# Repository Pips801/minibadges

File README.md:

# SAINTCON Minibadges
All of my Minibadges, including costs, files, and vendors.

# 2026

## IPEX to SMA adapter Minibadge
### Images

### Description
A minibadge (meant for use with my Meshtastic Minibadge) that converts I-PEX to SMA, so you can have a vertical SMA antenna.

## Phone charger Minibadge
### Images

### Description
Have you ever needed to charge your phone (or other stuff), but all you have lying around is a SAINTCON badge? You’re in luck! This minibadge will charge (up to 500mA) anything USB-C that you plug into it! Charge your phone! Charge your headphones! Charge a laptop! (not really) Charge another badge! The world is your ~oyster~ charger!

## BOM (post-tariffs)
| Vendor          | Item                   | Item total | Item quantity | Per item cost | Per unit cost | Per unit required |
| --------------- | ---------------------- | ---------- | ------------- | ------------- | ------------- | ----------------- |
| JLC PCB         | Board                  | $5.00      | 30            | $0.17         | $0.17         | 1                 |
| JLC Assembly    | Setup fee              | $8.00      | 30            | $0.27         | $0.27         | 1                 |
| JLC Assembly    | Stencil                | $1.50      | 30            | $0.05         | $0.05         | 1                 |
| JLC Assembly    | Components             | $17.11     | 30            | $0.57         | $0.57         | 1                 |
| JLC Assembly    | Extended component fee | $12.00     | 30            | $0.40         | $0.40         | 1                 |
| JLC Assembly    | Assembly fee           | $2.29      | 30            | $0.08         | $0.08         | 1                 |
| Shipping        | Shipping               | $13.35     | 30            | $0.45         | $0.45         | 1                 |
| Tariffs & taxes | Sales Tax              | $4.08      | 30            | $0.14         | $0.14         | 1                 |

| Project total cost | Per unit total cost | Quantity | Adjusted total | Adjusted per unit cost |
| ------------------ | ------------------- | -------- | -------------- | ---------------------- |
| $63.33             | $2.11               | 30       | $63.33         | $2.11                  |

## Seeed XIAO ESP32 Minibadge
### Images

## Description
A Minibadge that can hold and power the Seeed XIAO ESP32 modules. It features 1206 diodes to prevent the XIAO from backfeeding power to the main badge, should you plug USB in at the same time. The Minibadge has solderable jumper pads to connect 3.3v, 5v, SDA, and SCL to your ESP. This is untested, and will be updated, but I recommend just soldering the 3.3V pad. I would like to see if it's at all possible for the badge next year to work with this badge over I2C.

Supports:
* [XIAO ESP32-S3 + Wio-SX1262 (Meshtastic)](https://www.seeedstudio.com/Wio-SX1262-with-XIAO-ESP32S3-p-5982.html)
* [XIAO ESP32-C6 (Thread/Zigbee)](https://www.seeedstudio.com/Seeed-Studio-XIAO-ESP32C6-p-5884.html)
* [XIAO ESP32-S3 Sense (Camera/SD card)](https://www.seeedstudio.com/XIAO-ESP32S3-Sense-p-5639.html)
* Other XIAO ESPs are untested, but if the pinout is the same, it will work.

Possible projects:
* [Meshtastic node minibadge](https://www.seeedstudio.com/Wio-SX1262-with-XIAO-ESP32S3-p-5982.html)
* [Zigbee node minibadge](https://www.seeedstudio.com/Seeed-Studio-XIAO-ESP32C6-p-5884.html)
* [Picture/video recorder minibadge](https://www.seeedstudio.com/XIAO-ESP32S3-Sense-p-5639.html)
* [LED matrix minibadge](https://www.seeedstudio.com/6x10-RGB-MATRIX-for-XIAO-p-5771.html)
* [GNSS minibadge](https://www.seeedstudio.com/L76K-GNSS-Module-for-Seeed-Studio-XIAO-p-5864.html)
* [Temp/humidity/light sensor minibadge](https://www.seeedstudio.com/XIAO-LOG-p-6341.html)
* [mmWave sensor minibadge](https://www.seeedstudio.com/Seeed-Studio-XIAO-24Ghz-mmwave-Human-Static-Presence-Module-p-6266.html)

# 2025

## Glitch Gallery
### Images

### Description
A secret Minibadge for a secret event. 

### BOM (post-tariffs)
| Vendor       | Item            | Item total | Item quantity | Per item cost | Per unit cost | Per unit required |
| ------------ | --------------- | ---------- | ------------- | ------------- | ------------- | ----------------- |
| JLC PCB      | Board           | $4.40      | 200           | $0.02         | $0.02         | 1                 |
| JLC PCB      | Engineering fee | $8.00      | 200           | $0.04         | $0.04         | 1                 |
| JLC PCB      | Deburring       | $4.30      | 200           | $0.02         | $0.02         | 1                 |
| JLC PCB      | Confirmation    | $1.00      | 200           | $0.01         | $0.01         | 1                 |
| JLC PCB      | Packaging       | $0.71      | 200           | $0.00         | $0.00         | 1                 |
| JLC PCB      | Film            | $0.20      | 200           | $0.00         | $0.00         | 1                 |
| JLC Tariffs  | Tariffs         | $10.23     | 200           | $0.05         | $0.05         | 1                 |
| JLC Shipping | Shipping        | $22.95     | 200           | $0.11         | $0.11         | 1                 |
| Amazon       | Bags            | $20.00     | 2000          | $0.01         | $0.01         | 1                 |
| Amazon       | Pins            | $39.00     | 16000         | $0.00         | $0.01         | 4                 |

| Quantity | Project total cost | Per unit total cost | Actual total | Actual per unit cost |
| -------- | ------------------ | ------------------- | ------------ | -------------------- |
| 200      | $110.79            | $0.55               | $55.74       | $0.28                |

## Microbadge Minibadge
### Images

### Description
A Minibadge that can hold 6 Microbadges! Supports the [Microbadge V2](https://github.com/Pips801/microbadge/) standard. This is my first 4 layer board!

### BOM (post-tariffs)
| Vendor       | Item            | Item total | Item quantity | Per item cost | Per unit cost | Per unit required |
| ------------ | --------------- | ---------- | ------------- | ------------- | ------------- | ----------------- |
| JLC PCB      | Board           | $6.90      | 250           | $0.03         | $0.03         | 1                 |
| JLC PCB      | Engineering fee | $24.00     | 250           | $0.10         | $0.10         | 1                 |
| JLC PCB      | Film            | $0.20      | 250           | $0.00         | $0.00         | 1                 |
| JLC PCB      | Testing         | $0.80      | 250           | $0.00         | $0.00         | 1                 |
| JLC PCB      | Deburring       | $5.40      | 250           | $0.02         | $0.02         | 1                 |
| JLC PCB      | Silkscreen tech | $16.20     | 250           | $0.06         | $0.06         | 1                 |
| JLC PCB      | Color           | $4.80      | 250           | $0.02         | $0.02         | 1                 |
| JLC Shipping | Shipping (UPS)  | $10.20     | 250           | $0.04         | $0.04         | 1                 |
| Amazon       | Bags            | $20.00     | 2000          | $0.01         | $0.01         | 1                 |
| Amazon       | Pins            | $39.00     | 16000         | $0.00         | $0.04         | 16                |

| Project total cost | Per unit total cost | Quantity | Adjusted total | Adjusted per unit cost |
| ------------------ | ------------------- | -------- | -------------- | ---------------------- |
| $127.50            | $0.28               | 450      | $145.35        | $0.32                  |

## Julia Reagan
### Images

### Description
Wife, Mother, and Grandmother. We will miss her!

### BOM (post-tariffs)
| Vendor       | Item                    | Item total | Item quantity | Per item cost | Per unit cost | Per unit required |
| ------------ | ----------------------- | ---------- | ------------- | ------------- | ------------- | ----------------- |
| JLC PCB      | Board                   | $25.50     | 450           | $0.06         | $0.06         | 1                 |
| JLC PCB      | Engineering fee         | $8.00      | 450           | $0.02         | $0.02         | 1                 |
| JLC PCB      | Film                    | $3.00      | 450           | $0.01         | $0.01         | 1                 |
| JLC PCB      | Confirm production file | $1.00      | 450           | $0.00         | $0.00         | 1                 |
| JLC PCB      | Silkscreen tech         | $4.72      | 450           | $0.01         | $0.01         | 1                 |
| JLC Assembly | Components              | $12.21     | 450           | $0.03         | $0.03         | 1                 |
| JLC Assembly | SMT assembly            | $5.70      | 450           | $0.01         | $0.01         | 1                 |
| JLC Assembly | Setup fee               | $25.00     | 450           | $0.06         | $0.06         | 1                 |
| JLC Assembly | Packaging fee           | $0.47      | 450           | $0.00         | $0.00         | 1                 |
| JLC Assembly | De-panel boards         | $17.29     | 450           | $0.04         | $0.04         | 1                 |
| JLC Assembly | Stencil                 | $7.89      | 450           | $0.02         | $0.02         | 1                 |
| JLC Assembly | Component fee           | $3.00      | 450           | $0.01         | $0.01         | 1                 |
| JLC Assembly | Confirm parts           | $0.43      | 450           | $0.00         | $0.00         | 1                 |
| JLC          | Shipping (UPS)          | $56.40     | 450           | $0.13         | $0.13         | 1                 |
| JLC          | Tariffs                 | $60.73     | 450           | $0.13         | $0.13         | 1                 |
| Amazon       | Bags                    | $19.99     | 2000          | $0.01         | $0.01         | 1                 |
| Amazon       | Pins                    | $39.00     | 16000         | $0.00         | $0.02         | 8                 |

| Project total cost | Per unit total cost | Quantity | Adjusted total | Adjusted per unit cost |
| ------------------ | ------------------- | -------- | -------------- | ---------------------- |
| $290.33            | $0.65               | 450      | $244.61        | $0.54                  |

## Crown Burger Minibadge
### Images
    
### Description
Do you love Fry sauce? because we sure do. We also love Crown Burger, whom we are beholdent to.

### BOM (post-tarrifs)
| Vendor | Item     | Item total | Item quantity | Per item cost | Per unit cost | Per unit required |
| ------ | -------- | ---------- | ------------- | ------------- | ------------- | ----------------- |
| JLCPCB | PCB      | $17.30     | 120           | $0.14         | $0.14         | 1                 |
| JLCPCB | Assembly | $32.96     | 120           | $0.27         | $0.27         | 1                 |
| JLCPCB | Shipping | $37.80     | 120           | $0.32         | $0.32         | 1                 |
| Amazon | Bags     | $19.99     | 2000          | $0.01         | $0.01         | 1                 |
| Amazon | Pins     | $39.00     | 16000         | $0.00         | $0.02         | 8                 |

| Project total cost | Per unit total cost | Quantity | Adjusted total | Adjusted per unit cost |
| ------------------ | ------------------- | -------- | -------------- | ---------------------- |
| $147.05            | $1.23               | 120      | $91.60         | $0.76                  |

## ATtiny DEVBOARD
### Images
     
### Description
ATTiny-816/1616 Minibadge Devboard with breakouts for USART, I2C, DAC, and SPI, as well as two LEDs. There is also support for two ADC (analog to digital conversion) inputs and two PTC (touch sense) pins. It is programmed using UPDI via pin 6 (PROG4). either has 8KB or 16KB of flash
### Assembly
Solder pin headers. DO NOT PLUG BOARD IN UPSIDE-DOWN!!!!
### BOM
| Description/Link 	| Item      	| Item total 	| Item quantity 	| Per item cost 	| Per unit cost 	|  Per unit required 	|
|------------------	|-----------	|------------	|---------------	|---------------	|---------------	|--------------------	|
| JLCPCB assembly  	| Minibadge 	|     $68.02 	|            50 	|         $1.36 	|         $1.36 	|                  1 	|
| Amazon           	| Pins      	|      $5.49 	|           800 	|         $0.01 	|         $0.11 	|                 16 	|

| Project total cost 	| Per unit total cost 	| Adjusted quantity 	| Adjusted total 	|
|--------------------	|---------------------	|-------------------	|----------------	|
|             $73.51 	|               $1.47 	|                50 	|         $73.51 	|

## BEEP BEEP Minibadge
### Images

### Descrption
An obnoxiously-loud buzzer with an obnoxiously bright and large button. How tempting! Who wouldn't want to press that? Due to the length of the buzzer, the minibadge needs extra-long pin headers to connect snug with the socket.
### Assembly Instructions
First, solder all of the LEDs and resistors. if you are missing R1 (a potentiometer), the simply bridge the pad that says "NO R1" with solder. The potentiometer is meant for volume control. Next, solder the buzzer on the back of the badge, then with some good cutters, snip the leads of the speaker as flush as you can get them. After that, solder the comically large button on the front.

## Problem Jeep
### Images
### Description
A reversable minibadge, first of its kind! It can be used both directions, and features LEDs and resistors especially for each orientation.

## 3x3 Minibadge Display
### Images

### Description
A 3x3 Minibadge display with the same clock module as the 10x10 minibadge grid.. The USB-C port is Charge only and is configured with a 5.1k pulldown resistor to request 5V, however you are limited to approx 500mA@3.3v from the DC-DC converter. 
### Assembly Instructions
Using a pre-soldered minibadge as a guide/holder, solder all pin sockets. Screw Acrylic plate on. Stick feet pads on bottom.

## 2x2 Minibadge Display
### Images

### Description
A compact 2x2 Minibadge display with the same clock module as the 10x10 minibadge grid. If this device works well, it can be scaled up to 10 minibadges (probaby 9, 3x3 grid) without changing out any components or altering the diagram. The USB-C port is Charge only and is configured with a 5.1k pulldown resistor to request 5V, however you are limited to approx 500mA from the DC-DC converter. 
### Assembly Instructions
Using a pre-soldered minibadge as a guide/holder, solder all pin sockets.

## Doug Dimmadome's Dimma-Minibadge
### Images

## Framework Laptop Expansion slot to Minibadge
### Images

### [Instructions](https://github.com/Pips801/minibadges/blob/main/Framework%20Expansion%20Card%20Minibadge/README.md)

## Flipper Zero to Minibadge add-on
### Images

### Instructions
Solder the 1x10 pin header row downwards. Solder the 2x 1x8 pin sockets facing upwards. Optionally, bridge the SDA and SCL pads and use a Flipper Zero app that can read I2C communications. Do not bridge the CLK pad - it does not work correctly for badges that use CLK for alternating light patters.

## I almost DIED at the CheckPoint party
### Images

### Description
Some poor soul partied so hard at the 2024 checkpoint party that they died. poor guy. This minibadge is in his honor. RIP.

## The Internet
### Images

### Description
This, Jen, is the Internet. 
### Assembly
First, solder the through-hole resistor on the back side of the minibadge, and then snip the legs around the front. Next, take the black box, and insert the LED into the hole in the box. Ensure that the LED is pushed down as far as it can be and is snug. Next, put the LED legs through the correct holes (long +, short -) and line up the LED and box on the board. Hot-glue/super-glue the box onto the board, and then solder the legs of the LED. Last, solder the Minibadge's pin legs. If assembled correctly, it should blink red on and off (the LED has an IC that makes it blink)
### BOM
| Description/Link 	| Item 	| Item total 	| Item quantity 	| Per item cost 	| Per unit cost 	|  Per unit required 	|
|------------------	|------	|------------	|---------------	|---------------	|---------------	|--------------------	|
| JLCPCB           	| PCBs 	|      $9.93 	|           100 	|         $0.10 	|         $0.10 	|                  1 	|
| Amazon           	| LEDs 	|      $5.99 	|           100 	|         $0.06 	|         $0.06 	|                  1 	|

## Hang in there!
### Images

### Description
Hang in there! You've got this!
### BOM
| Description/Link  	| Item 	| Item total 	| Item quantity 	| Per item cost 	| Per unit cost 	|  Per unit required 	|
|-------------------	|------	|------------	|---------------	|---------------	|---------------	|--------------------	|
| JLCPCB + Assembly 	| PCBs 	|    $130.80 	|           400 	|         $0.33 	|         $0.33 	|                  1 	|

## Bible Study at ABGs
### Images

### Description
Sacrilegious Minibadge. You can only get this minibadge if you go to the one bar in provo during SAINTCON. If I see you're from the con, I'll give you one.
### BOM
| Description/Link  	| Item 	| Item total 	| Item quantity 	| Per item cost 	| Per unit cost 	|  Per unit required 	|
|-------------------	|------	|------------	|---------------	|---------------	|---------------	|--------------------	|
| JLCPCB + Assembly 	| PCBs 	|     $33.79 	|            50 	|         $0.68 	|         $0.68 	|                  1 	|
| Amazon            	| Bags 	|      $5.05 	|           100 	|         $0.05 	|         $0.05 	|                  1 	|
| Amazon            	| Pins 	|      $5.49 	|           800 	|         $0.01 	|         $0.05 	|                  8 	|

| Project total cost 	| Per unit total cost 	| Adjusted quantity 	| Adjusted total 	|
|--------------------	|---------------------	|-------------------	|----------------	|
|             $44.33 	|               $0.78 	|                50 	|         $39.06 	|

## Full Color Pipscat
### Images

### Description
Full color silkscreening process. The process sucked, and I was forced to learn EasyEDA in order to generate the files that JLCPCB will accept (surprise, it's super annoying and even if you do it right, it goes wrong.) 
The whole process sucked, and while I'm excited to have these badges, I am gonna make hamster handle the BS  of color silkscreening. Maybe I can have boards assembled for cheap and then just ship them over to him.
### BOM
| Description/Link | Item | Item total | Item quantity | Per item cost | Per unit cost |  Per unit required |
|------------------|------|------------|---------------|---------------|---------------|--------------------|
| JLCPCB           | PCBs |     $35.02 |           300 |         $0.12 |         $0.12 |                  1 |

## Scratch and Sniff
### Images

### Description
A scratch and sniff minibadgebadge. Stupid idea that came about from 801 Labs. The badge has a very small scratch and sniff sticker overlayed on the front. The sticker will be one of the 5 scents I used for this project, as follows

- DNS (Wet Dirt)
- TOR (Onion)
- Zodiak's Sandals (Cheese)
- Magic Smoke (Burnt Rubber)
- Vendor Call (Manure)
  
Honestly, they all smell bad. (which was the point) I may make a second round that smells nice, that would be easier to work with.
### BOM
| Description/Link  | Item                     | Item total | Item quantity | Per item cost | Per unit cost |  Per unit required |
|-------------------|--------------------------|------------|---------------|---------------|---------------|--------------------|
| JLCPCB + Assembly | PCBs                     |    $148.34 |           400 |         $0.37 |         $0.37 |                  1 |
| Amazon            | Bags                     |     $20.00 |           400 |         $0.05 |         $0.05 |                  1 |
| Amazon            | Pins                     |     $21.96 |          3200 |         $0.01 |         $0.05 |                  8 |
| Print-a-Scent     | Scratch-n-Sniff Stickers |        $74 |           750 |         $0.10 |         $0.10 |                  1 |

| Project total cost | Per unit total cost | Adjusted quantity | Adjusted total |
|--------------------|---------------------|-------------------|----------------|
|            $264.30 |               $0.57 |               400 |        $229.77 |

# 2024

## BLANK_BADGE V3 (White and Black)
### Images

### Description
Revamped BLANK_BADGE, this time with two different colors. I messed up my board shop settings on this one, and they helpfully made them sinly pannels. I tried to get them to do it again but they have minimum sizes and I was unable to intentionally do this again.
### BOM
| Description/Link | Item | Item total | Item quantity | Per item cost | Per unit cost |  Per unit required |
|------------------|------|------------|---------------|---------------|---------------|--------------------|
| JLCPCB + Assembly | PCBs |     $61.26 |            60 |         $1.02 |         $1.02 |                  1 |
| Amazon           | Bags |      $5.05 |           100 |         $0.05 |         $0.05 |                  1 |
| Amazon           | Pins |      $5.49 |           800 |         $0.01 |         $0.05 |                  8 |

| Project total cost | Per unit total cost | Adjusted quantity | Adjusted total |
|--------------------|---------------------|-------------------|----------------|
|             $71.80 |               $1.13 |                60 |         $67.58 |

## Blank Badge V1 30ct (My first badge!)
### Images

### Description
My first ever circuit board! I made this in under 24 hours, starting at nothing.
### BOM
| Description/Link | Item     | Item total | Item quantity | Per item cost | Per unit cost |  Per unit required |
|------------------|----------|------------|---------------|---------------|---------------|--------------------|
| JLCPCB           | PCBs     |     $22.48 |            30 |         $0.75 |         $0.75 |                  1 |
| Amazon           | Bags     |      $5.05 |           100 |         $0.05 |         $0.05 |                  1 |
| Amazon           | LED      |      $9.99 |           100 |         $0.10 |         $0.10 |                  1 |
| Amazon           | Resistor |      $7.09 |           100 |         $0.07 |         $0.07 |                  1 |
| Amazon           | Pins     |      $5.49 |           800 |         $0.01 |         $0.05 |                  8 |

| Project total cost | Per unit total cost | Adjusted quantity | Adjusted total |
|--------------------|---------------------|-------------------|----------------|
|             $50.10 |               $1.03 |                30 |         $30.77 |

### Other Details

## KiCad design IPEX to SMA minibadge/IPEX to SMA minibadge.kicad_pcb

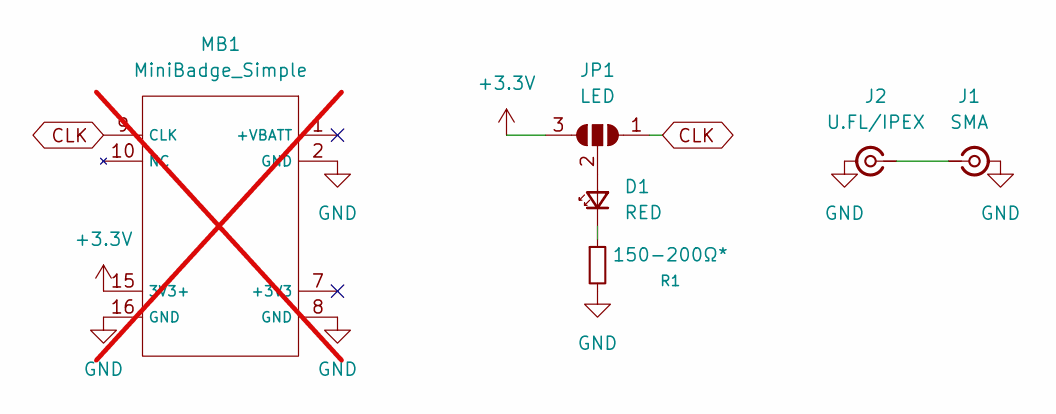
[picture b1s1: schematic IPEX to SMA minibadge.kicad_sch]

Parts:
D1: RED; LED_0805_2012Metric; LCSC Part # C84256
J1: SMA; SMA_Amphenol_132289_EdgeMount; LCSC Part # C5301850
J2: U.FL/IPEX; U.FL_Hirose_U.FL-R-SMT-1_Vertical; LCSC Part # C19078354
JP1: LED; SolderJumper-3_P1.3mm_Open_RoundedPad1.0x1.5mm_NumberLabels
MB1: MiniBadge_Simple; MiniBadge_Simple_NoEdges; not fitted
R1: 150-200Ω*; R_0603_1608Metric; LCSC Part # C22808

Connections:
+3.3V: JP1.3 (B), MB1.15 (3V3+)
CLK: JP1.1 (A), MB1.9 (CLK)
GND: J1.2 (Ext), J2.2 (Ext), MB1.2 (GND), MB1.8 (GND), MB1.16 (GND), R1.2
unnamed: D1.2 (A), JP1.2 (C)
unnamed: D1.1 (K), R1.1
unnamed: J1.1 (In), J2.1 (In)

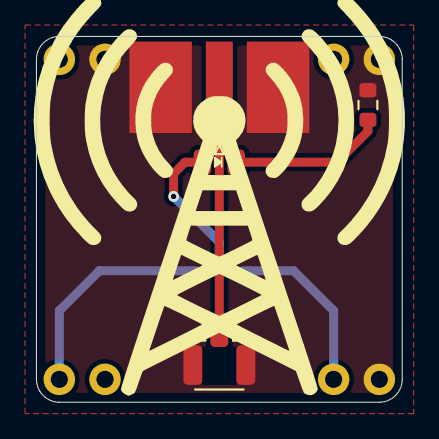
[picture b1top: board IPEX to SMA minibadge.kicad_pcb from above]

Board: 2 copper layers, 20.3 x 20.3 mm, 6 parts (1 on the bottom side), 6 nets.

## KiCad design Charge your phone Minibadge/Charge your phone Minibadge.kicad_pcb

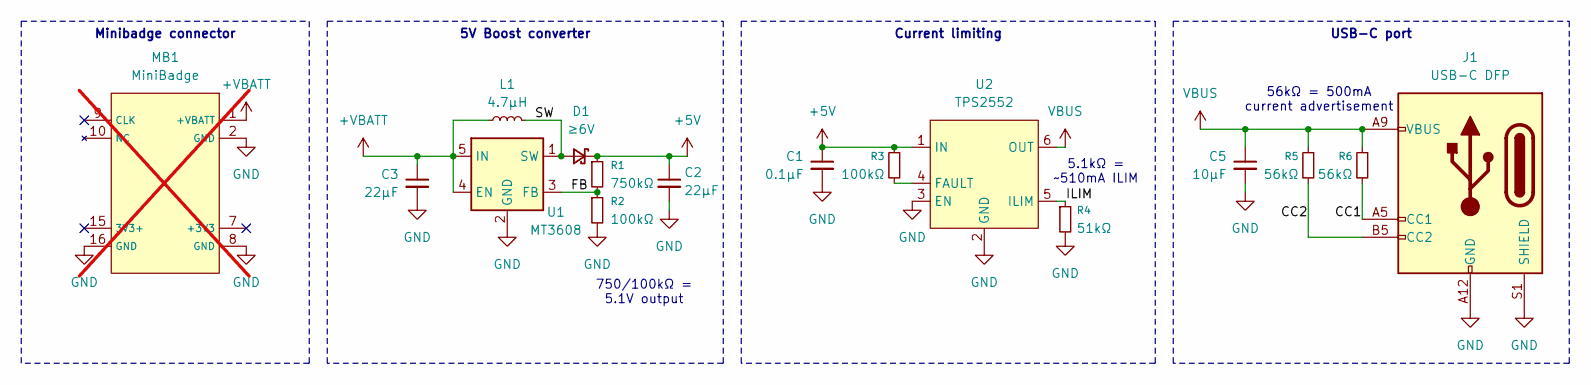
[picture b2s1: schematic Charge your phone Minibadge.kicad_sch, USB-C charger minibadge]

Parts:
C1: 0.1μF; C_0603_1608Metric; LCSC Part # C14663
C2, C3: 22μF; C_1206_3216Metric; LCSC Part # C12891
C5: 10μF; C_0603_1608Metric; LCSC Part # C96446
D1: ≥6V; D_SOD-123; LCSC Part # C7420328
J1: USB-C DFP; USB_C_Receptacle_HRO_TYPE-C-31-M-17; LCSC Part # C283540
L1: 4.7μH; L_Taiyo-Yuden_MD-4040; LCSC Part # C602031
MB1: MiniBadge; MiniBadge_Simple_NoEdges; not fitted
R1: 750kΩ; R_0603_1608Metric; LCSC Part # C23240
R2, R3: 100kΩ; R_0603_1608Metric; LCSC Part # C25803
R4: 51kΩ; R_0603_1608Metric; LCSC Part # C23196
R5, R6: 56kΩ; R_0603_1608Metric; LCSC Part # C23206
U1: MT3608; SOT-23-6; LCSC Part # C84817
U2: TPS2552; SOT-23-6; LCSC Part # C46506

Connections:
+5V: C1.1, C2.1, D1.1 (K), R1.1, R3.1, U2.1 (IN)
+VBATT: C3.1, L1.1, MB1.1 (+VBATT), U1.4 (EN), U1.5 (IN)
/CC1: J1.A5 (CC1), R6.2
/CC2: J1.B5 (CC2), R5.2
/FB: R1.2, R2.1, U1.3 (FB)
/ILIM: R4.1, U2.5 (ILIM)
/SW: D1.2 (A), L1.2, U1.1 (SW)
GND: C1.2, C2.2, C3.2, C5.2, J1.A12 (GND), J1.B12 (GND), J1.S1 (SHIELD), MB1.2 (GND), MB1.8 (GND), MB1.16 (GND), R2.2, R4.2, U1.2 (GND), U2.2 (GND), U2.3 (EN)
unnamed: R3.2, U2.4 (FAULT)
VBUS: C5.1, J1.A9 (VBUS), J1.B9 (VBUS), R5.1, R6.1, U2.6 (OUT)

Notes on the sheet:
750/100kΩ = 5.1V output
56kΩ = 500mA current advertisement
5.1kΩ = ~510mA ILIM
Minibadge connector
5V Boost converter
Current limiting
USB-C port

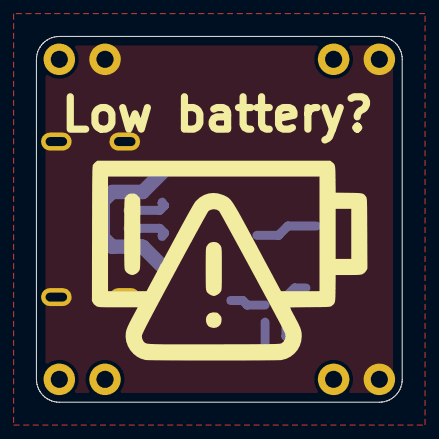
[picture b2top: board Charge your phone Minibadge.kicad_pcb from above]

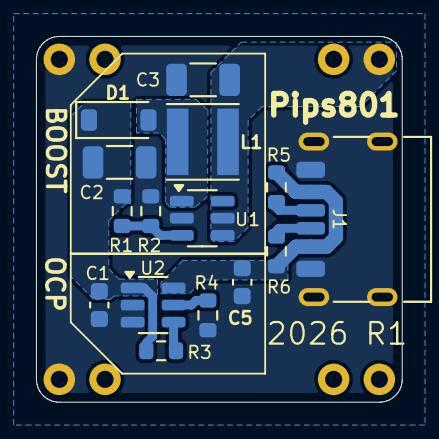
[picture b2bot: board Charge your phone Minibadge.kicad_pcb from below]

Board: 2 copper layers, 20.3 x 20.3 mm, 16 parts (15 on the bottom side), 10 nets.

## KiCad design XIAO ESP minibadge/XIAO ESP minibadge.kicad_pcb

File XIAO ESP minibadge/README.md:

## Seeed XIAO ESP32 Minibadge
### Images

## Description
A Minibadge that can hold and power the Seeed XIAO ESP32 modules. It features 1206 diodes to prevent the XIAO from backfeeding power to the main badge, should you plug USB in at the same time. The Minibadge has solderable jumper pads to connect 3.3v, 5v, SDA, and SCL to your ESP. This is untested, and will be updated, but I recommend just soldering the 3.3V pad. I would like to see if it's at all possible for the badge next year to work with this badge over I2C.

Supports:
* [XIAO ESP32-S3 + Wio-SX1262 (Meshtastic)](https://www.seeedstudio.com/Wio-SX1262-with-XIAO-ESP32S3-p-5982.html)
* [XIAO ESP32-C6 (Thread/Zigbee)](https://www.seeedstudio.com/Seeed-Studio-XIAO-ESP32C6-p-5884.html)
* [XIAO ESP32-S3 Sense (Camera/SD card)](https://www.seeedstudio.com/XIAO-ESP32S3-Sense-p-5639.html)
* Other XIAO ESPs are untested, but if the pinout is the same, it will work.

Possible projects:
* [Meshtastic node minibadge](https://www.seeedstudio.com/Wio-SX1262-with-XIAO-ESP32S3-p-5982.html)
* [Zigbee node minibadge](https://www.seeedstudio.com/Seeed-Studio-XIAO-ESP32C6-p-5884.html)
* [Picture/video recorder minibadge](https://www.seeedstudio.com/XIAO-ESP32S3-Sense-p-5639.html)
* [LED matrix minibadge](https://www.seeedstudio.com/6x10-RGB-MATRIX-for-XIAO-p-5771.html)
* [GNSS minibadge](https://www.seeedstudio.com/L76K-GNSS-Module-for-Seeed-Studio-XIAO-p-5864.html)
* [Temp/humidity/light sensor minibadge](https://www.seeedstudio.com/XIAO-LOG-p-6341.html)
* [mmWave sensor minibadge](https://www.seeedstudio.com/Seeed-Studio-XIAO-24Ghz-mmwave-Human-Static-Presence-Module-p-6266.html)

## Flashing The XIAO ESP32S3
Flashing the XIAO ESP32S3 is incredibly straightforward, following the standard procedure for ESP32 devices:

* Connect the Device: Use a USB Type-C cable that supports data transfer to connect the device to your computer.
* Visit the Flasher Tool: Open [Meshtastic Flasher](https://flasher.meshtastic.org/).
* Select Your Device: From the device list, choose Seeed Xiao ESP32-S3.
* hoose Firmware: Select your preferred firmware version and click on Flash.
* Review Changelog: The tool will display a changelog—click Continue.
* Perform Full Erase: For the best results, select Full Erase and Install, then click Update.
* Reboot: Once the device reboots, it’s ready to pair.

## Pairing the Device
Pairing the XIAO ESP32S3 with the Meshtastic app is as simple as with any other Meshtastic device:

* Download the Meshtastic App: Available on both the App Store (iOS) and Google Play (Android).
* Bluetooth Pairing: Open the Meshtastic app and navigate to the Bluetooth page. Wait a moment for your XIAO ESP32S3 to appear in the list of available devices. It will display a Node ID and additional details in the app.
* Enter Pairing Code: Select the XIAO ESP32S3 from the list and enter the pairing code 123456 when prompted. If it’s not 123456, check the terminal output after flashing to find the correct pairing code.
* Set Region: After pairing, you’ll be prompted to select your region. Choose the appropriate setting for your location. The device will restart to apply the region settings.

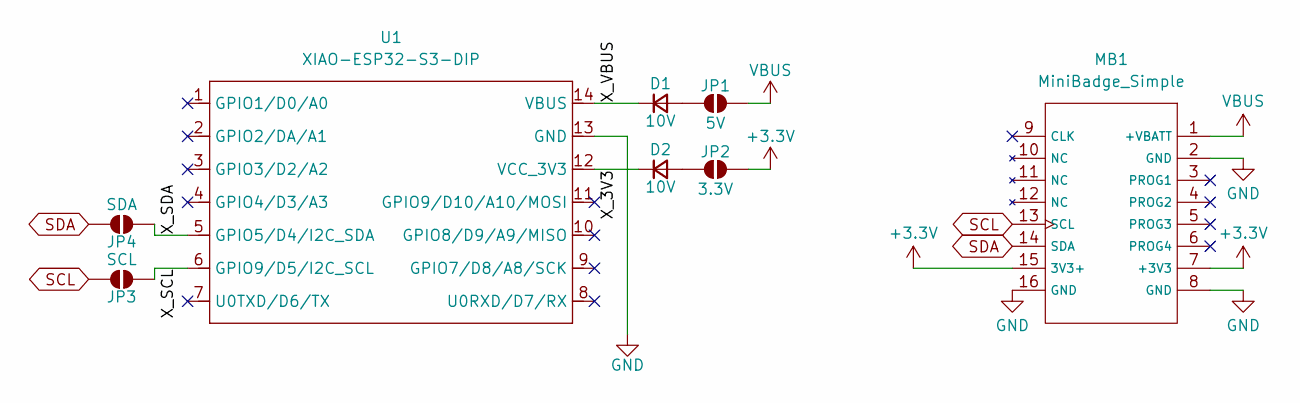
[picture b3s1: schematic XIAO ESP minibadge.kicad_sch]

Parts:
D1, D2: 10V; D_1206_3216Metric_Pad1.42x1.75mm_HandSolder
JP1: 5V; SolderJumper-2_P1.3mm_Open_TrianglePad1.0x1.5mm
JP2: 3.3V; SolderJumper-2_P1.3mm_Open_TrianglePad1.0x1.5mm
JP3: SCL; SolderJumper-2_P1.3mm_Open_TrianglePad1.0x1.5mm
JP4: SDA; SolderJumper-2_P1.3mm_Open_TrianglePad1.0x1.5mm
MB1: MiniBadge_Simple; MiniBadge_Full_NoEdges
U1: XIAO-ESP32-S3-DIP; XIAO-ESP32S3-DIP

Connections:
+3.3V: JP2.2 (B), MB1.7 (+3V3), MB1.15 (3V3+)
/X_3V3: D2.1 (K), U1.12 (VCC_3V3)
/X_SCL: JP3.1 (A), U1.6 (GPIO9/D5/I2C_SCL)
/X_SDA: JP4.1 (A), U1.5 (GPIO5/D4/I2C_SDA)
/X_VBUS: D1.1 (K), U1.14 (VBUS)
GND: MB1.2 (GND), MB1.8 (GND), MB1.16 (GND), U1.13 (GND)
unnamed: D1.2 (A), JP1.1 (A)
unnamed: D2.2 (A), JP2.1 (A)
SCL: JP3.2 (B), MB1.13 (SCL)
SDA: JP4.2 (B), MB1.14 (SDA)
VBUS: JP1.2 (B), MB1.1 (+VBATT)

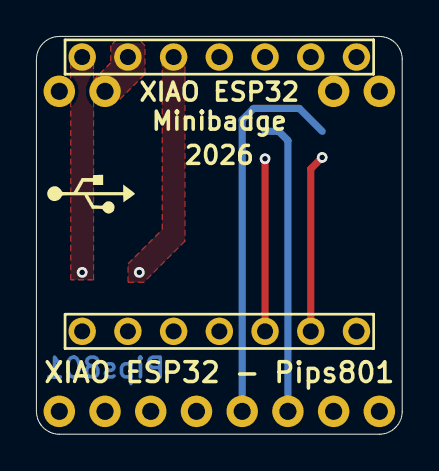
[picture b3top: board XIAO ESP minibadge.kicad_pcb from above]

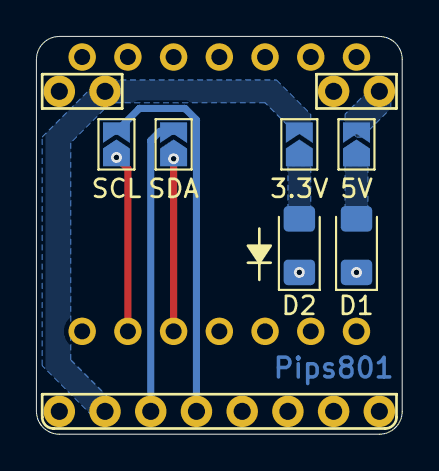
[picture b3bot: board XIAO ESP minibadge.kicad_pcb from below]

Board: 2 copper layers, 20.3 x 22.1 mm, 8 parts (6 on the bottom side), 11 nets.

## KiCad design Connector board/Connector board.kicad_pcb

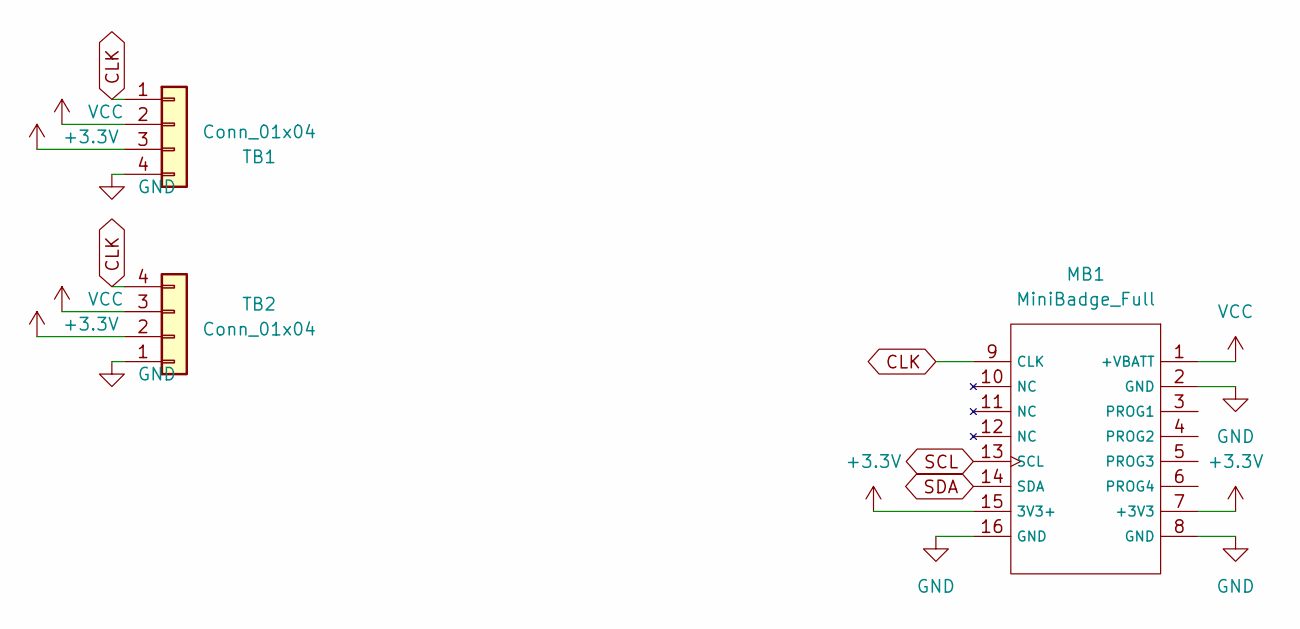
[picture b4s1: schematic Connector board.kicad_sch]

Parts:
MB1: MiniBadge_Full; MiniBadge_Slot_Reflective
TB1, TB2: Conn_01x04; JST_GH_SM04B-GHS-TB_1x04-1MP_P1.25mm_Horizontal

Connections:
+3.3V: MB1.7 (+3V3), MB1.15 (3V3+), TB1.3, TB2.2
CLK: MB1.9 (CLK), TB1.1, TB2.4
GND: MB1.2 (GND), MB1.8 (GND), MB1.16 (GND), TB1.4, TB2.1
SCL: MB1.13 (SCL)
SDA: MB1.14 (SDA)
VCC: MB1.1 (+VBATT), TB1.2, TB2.3

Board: 4 copper layers, 3 parts (0 on the bottom side), 4 nets, no tracks yet.

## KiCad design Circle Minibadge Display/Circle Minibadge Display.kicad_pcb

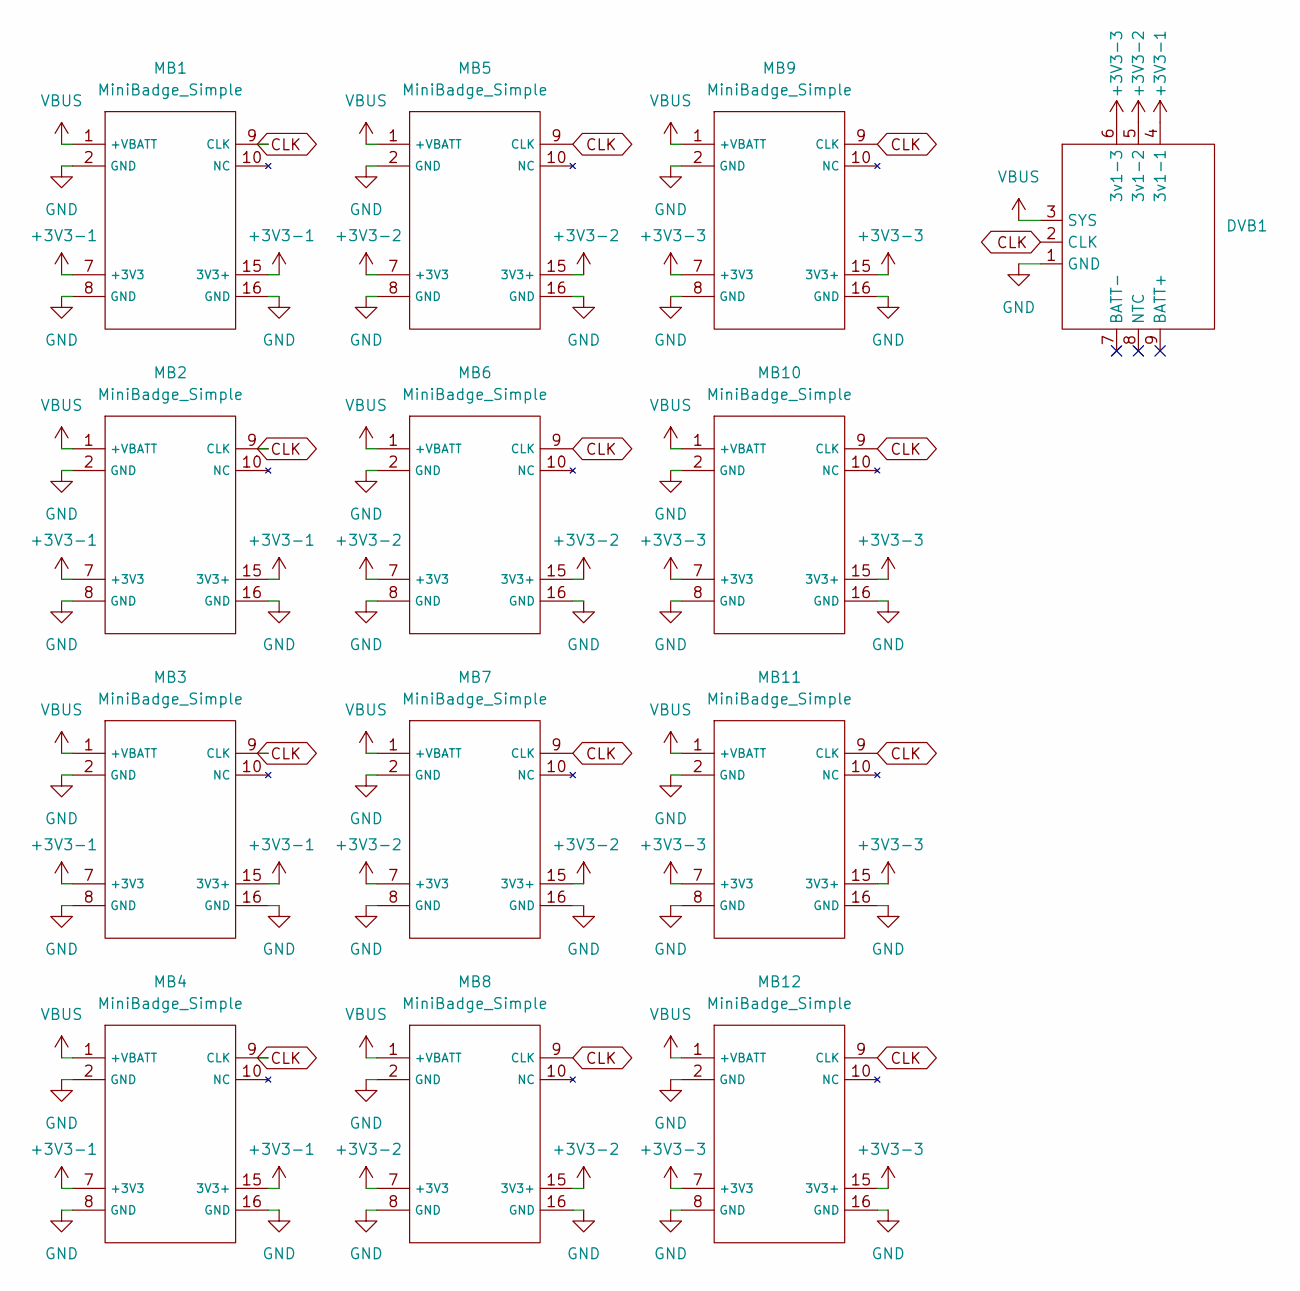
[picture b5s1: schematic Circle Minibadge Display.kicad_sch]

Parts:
DVB1: Minibadge Devboard
MB1, MB2, MB3, MB4, MB5, MB6, MB7, MB8, MB9, MB10, MB11, MB12: MiniBadge_Simple; MiniBadge_Slot_Basic

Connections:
+3V3-1: DVB1.4 (3v1-1), MB1.7 (+3V3), MB1.15 (3V3+), MB2.7 (+3V3), MB2.15 (3V3+), MB3.7 (+3V3), MB3.15 (3V3+), MB4.7 (+3V3), MB4.15 (3V3+)
+3V3-2: DVB1.5 (3v1-2), MB5.7 (+3V3), MB5.15 (3V3+), MB6.7 (+3V3), MB6.15 (3V3+), MB7.7 (+3V3), MB7.15 (3V3+), MB8.7 (+3V3), MB8.15 (3V3+)
+3V3-3: DVB1.6 (3v1-3), MB9.7 (+3V3), MB9.15 (3V3+), MB10.7 (+3V3), MB10.15 (3V3+), MB11.7 (+3V3), MB11.15 (3V3+), MB12.7 (+3V3), MB12.15 (3V3+)
CLK: DVB1.2 (CLK), MB1.9 (CLK), MB2.9 (CLK), MB3.9 (CLK), MB4.9 (CLK), MB5.9 (CLK), MB6.9 (CLK), MB7.9 (CLK), MB8.9 (CLK), MB9.9 (CLK), MB10.9 (CLK), MB11.9 (CLK), MB12.9 (CLK)
GND: DVB1.1 (GND), MB1.2 (GND), MB1.8 (GND), MB1.16 (GND), MB2.2 (GND), MB2.8 (GND), MB2.16 (GND), MB3.2 (GND), MB3.8 (GND), MB3.16 (GND), MB4.2 (GND), MB4.8 (GND), MB4.16 (GND), MB5.2 (GND), MB5.8 (GND), MB5.16 (GND), MB6.2 (GND), MB6.8 (GND), MB6.16 (GND), MB7.2 (GND), MB7.8 (GND), MB7.16 (GND), MB8.2 (GND), MB8.8 (GND), MB8.16 (GND), MB9.2 (GND), MB9.8 (GND), MB9.16 (GND), MB10.2 (GND), MB10.8 (GND), MB10.16 (GND), MB11.2 (GND), MB11.8 (GND), MB11.16 (GND), MB12.2 (GND), MB12.8 (GND), MB12.16 (GND)
VBUS: DVB1.3 (SYS), MB1.1 (+VBATT), MB2.1 (+VBATT), MB3.1 (+VBATT), MB4.1 (+VBATT), MB5.1 (+VBATT), MB6.1 (+VBATT), MB7.1 (+VBATT), MB8.1 (+VBATT), MB9.1 (+VBATT), MB10.1 (+VBATT), MB11.1 (+VBATT), MB12.1 (+VBATT)

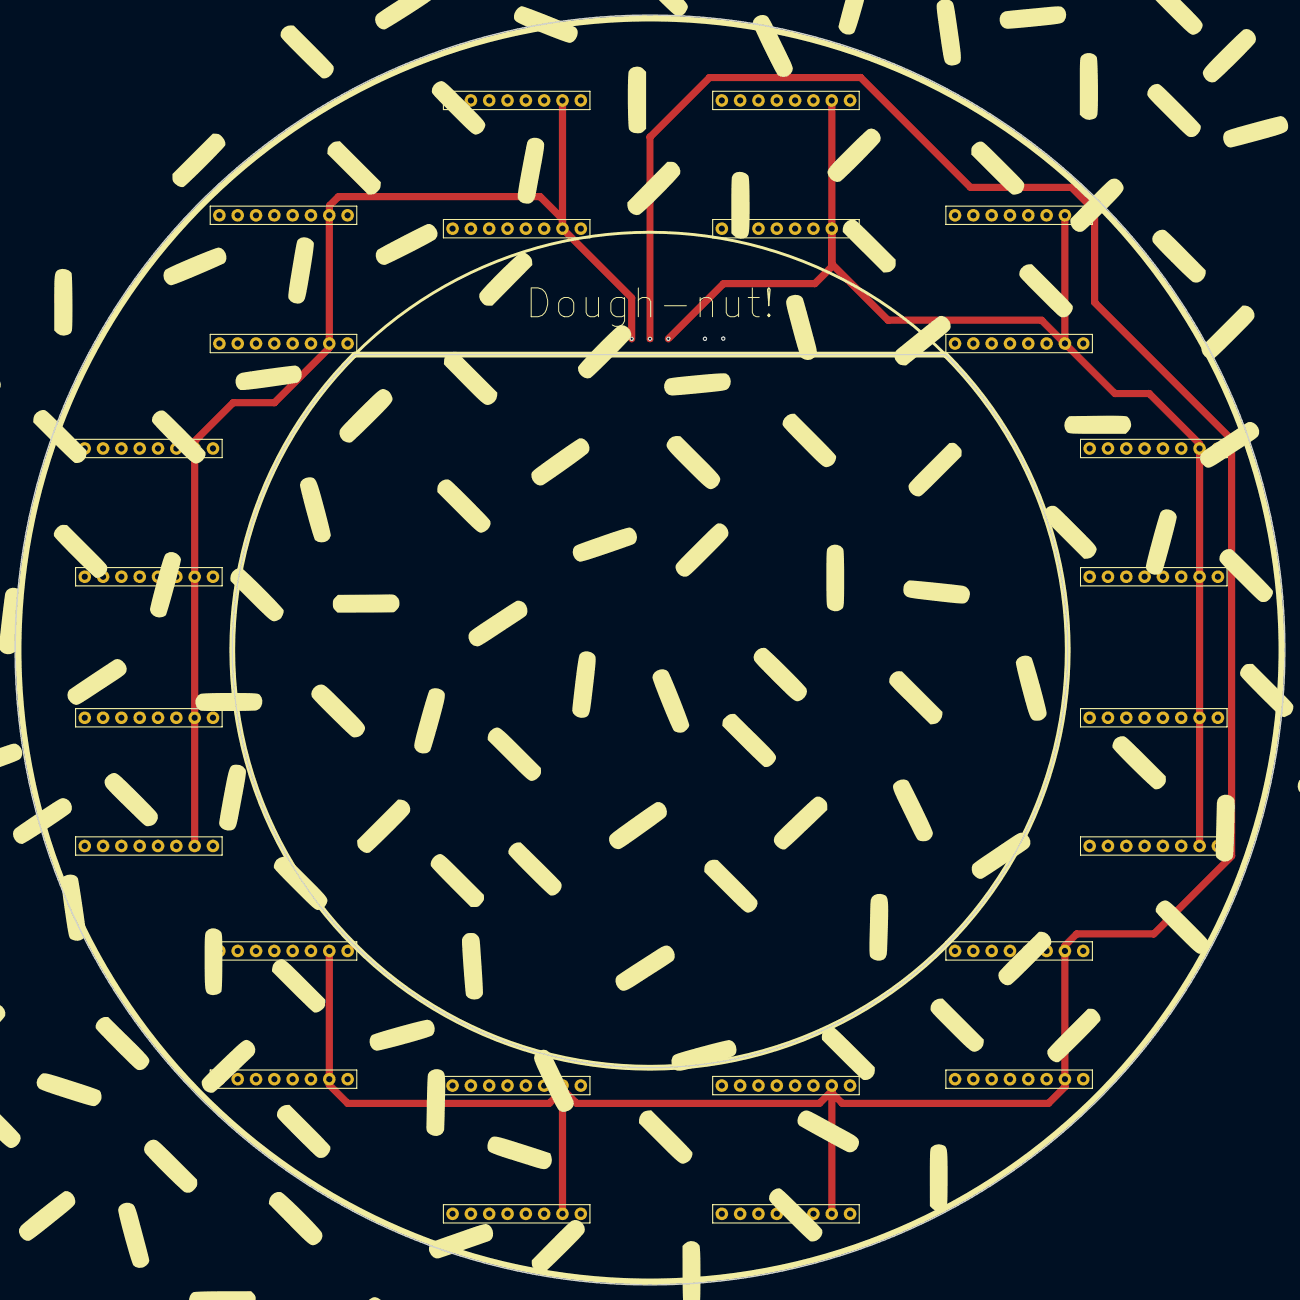
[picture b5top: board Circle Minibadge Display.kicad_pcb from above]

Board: 4 copper layers, 176.0 x 176.0 mm, 13 parts (1 on the bottom side), 6 nets.

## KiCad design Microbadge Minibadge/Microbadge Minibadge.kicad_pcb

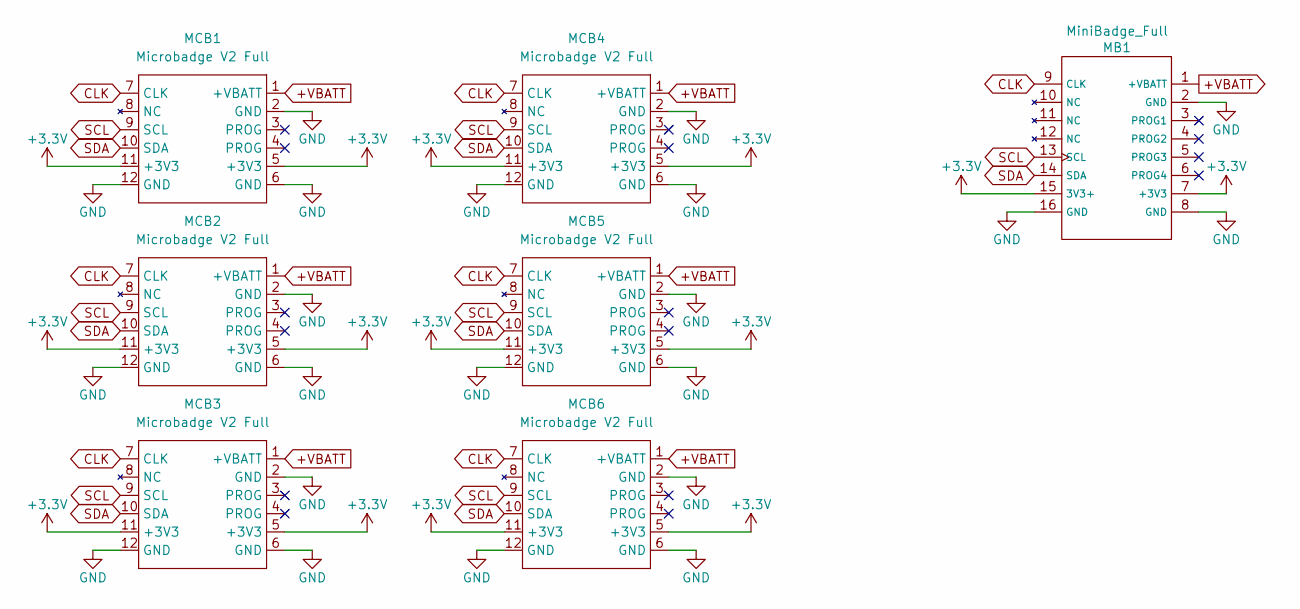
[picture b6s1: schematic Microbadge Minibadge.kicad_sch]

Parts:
MB1: MiniBadge_Full
MCB1, MCB2, MCB3, MCB4, MCB5, MCB6: Microbadge V2 Full; Microbadge_V2_full_round_socket_reflective_nosilk_GND

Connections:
+3.3V: MB1.7 (+3V3), MB1.15 (3V3+), MCB1.5 (+3V3), MCB1.11 (+3V3), MCB2.5 (+3V3), MCB2.11 (+3V3), MCB3.5 (+3V3), MCB3.11 (+3V3), MCB4.5 (+3V3), MCB4.11 (+3V3), MCB5.5 (+3V3), MCB5.11 (+3V3), MCB6.5 (+3V3), MCB6.11 (+3V3)
+VBATT: MB1.1 (+VBATT), MCB1.1 (+VBATT), MCB2.1 (+VBATT), MCB3.1 (+VBATT), MCB4.1 (+VBATT), MCB5.1 (+VBATT), MCB6.1 (+VBATT)
CLK: MB1.9 (CLK), MCB1.7 (CLK), MCB2.7 (CLK), MCB3.7 (CLK), MCB4.7 (CLK), MCB5.7 (CLK), MCB6.7 (CLK)
GND: MB1.2 (GND), MB1.8 (GND), MB1.16 (GND), MCB1.2 (GND), MCB1.6 (GND), MCB1.12 (GND), MCB2.2 (GND), MCB2.6 (GND), MCB2.12 (GND), MCB3.2 (GND), MCB3.6 (GND), MCB3.12 (GND), MCB4.2 (GND), MCB4.6 (GND), MCB4.12 (GND), MCB5.2 (GND), MCB5.6 (GND), MCB5.12 (GND), MCB6.2 (GND), MCB6.6 (GND), MCB6.12 (GND)
SCL: MB1.13 (SCL), MCB1.9 (SCL), MCB2.9 (SCL), MCB3.9 (SCL), MCB4.9 (SCL), MCB5.9 (SCL), MCB6.9 (SCL)
SDA: MB1.14 (SDA), MCB1.10 (SDA), MCB2.10 (SDA), MCB3.10 (SDA), MCB4.10 (SDA), MCB5.10 (SDA), MCB6.10 (SDA)

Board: 4 copper layers, 7 parts (0 on the bottom side), 6 nets, no tracks yet.

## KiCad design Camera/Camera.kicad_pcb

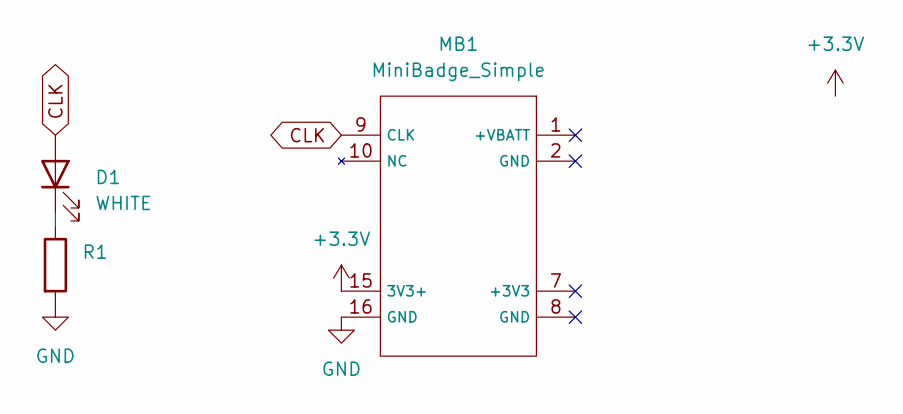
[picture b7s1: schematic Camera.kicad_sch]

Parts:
D1: WHITE; LED_1206_3216Metric
MB1: MiniBadge_Simple; MiniBadge_Simple_NoEdges
R1: R_1206_3216Metric

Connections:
+3.3V: MB1.15 (3V3+)
CLK: D1.2 (A), MB1.9 (CLK)
GND: MB1.16 (GND), R1.2
unnamed: D1.1 (K), R1.1

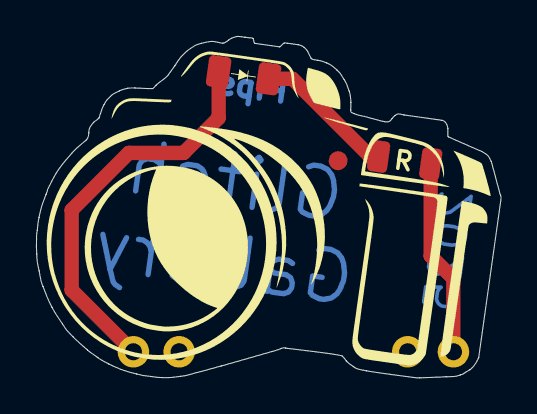
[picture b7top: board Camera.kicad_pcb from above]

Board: 2 copper layers, 25.8 x 19.0 mm, 3 parts (0 on the bottom side), 3 nets.

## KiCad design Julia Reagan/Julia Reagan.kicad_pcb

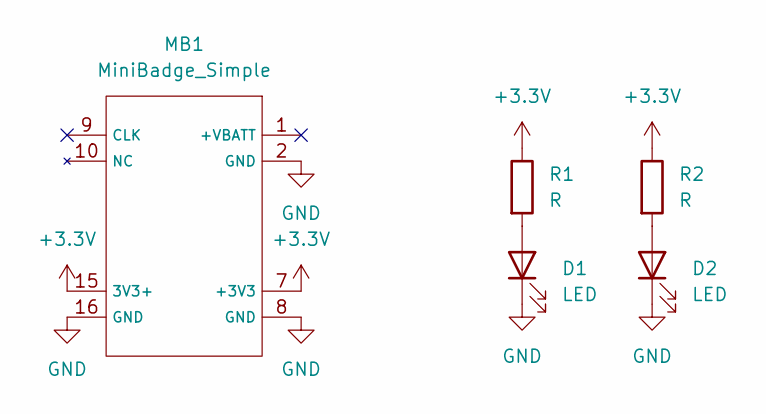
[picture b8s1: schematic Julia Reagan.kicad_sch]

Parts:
D1, D2: LED; LED_1206_3216Metric
MB1: MiniBadge_Simple; MiniBadge_Simple_NoEdges
R1, R2: R; R_1206_3216Metric

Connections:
+3.3V: MB1.7 (+3V3), MB1.15 (3V3+), R1.1, R2.1
GND: D1.1 (K), D2.1 (K), MB1.2 (GND), MB1.8 (GND), MB1.16 (GND)
unnamed: D1.2 (A), R1.2
unnamed: D2.2 (A), R2.2

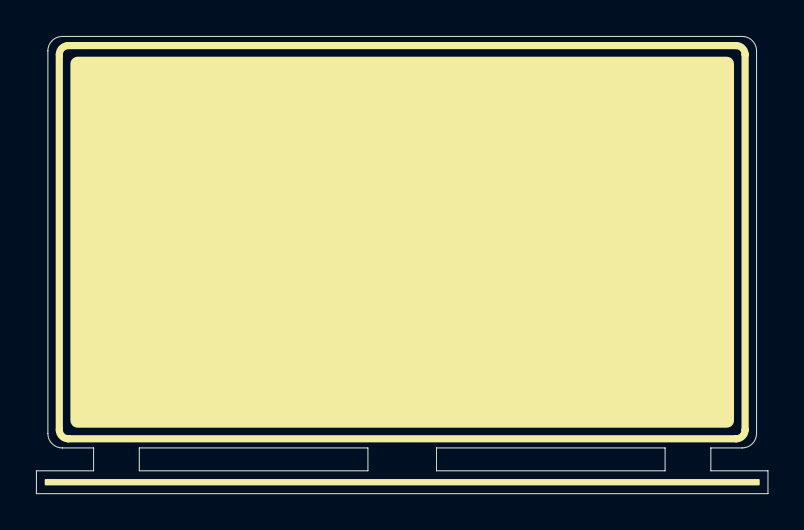
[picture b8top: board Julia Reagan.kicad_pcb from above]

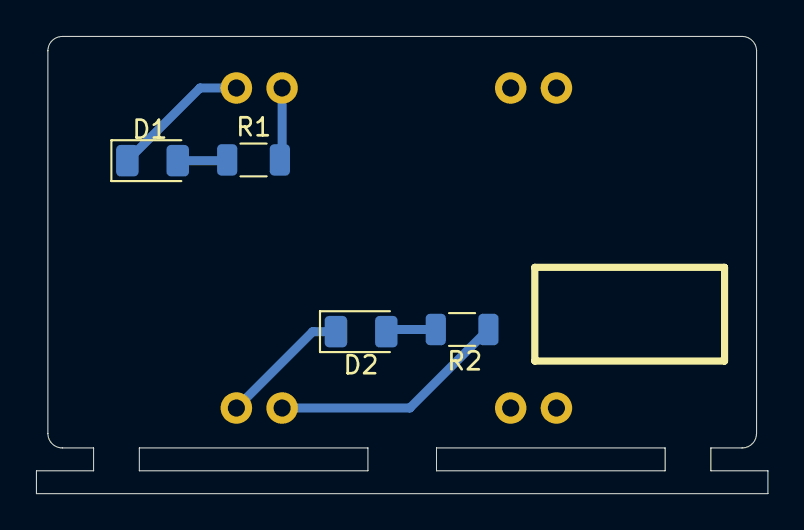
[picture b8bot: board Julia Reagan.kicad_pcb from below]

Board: 2 copper layers, 40.6 x 25.4 mm, 5 parts (4 on the bottom side), 4 nets.

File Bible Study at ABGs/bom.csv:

Designator,Footprint,Quantity,Value,LCSC Part #
D1_R,1206,1,LED_R,
"D2_W, D3_W",1206,2,LED_W,
R1,1206,1,R_100Ω,
R2,1206,1,R_10Ω,
X1,SAINTCON-Minibadge-Simple,1,SAINTCON-Minibadge-Simple,

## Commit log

2024-10-29 Create README.md pipscat
2024-10-29 upload pipscat minibadge files
2024-10-30 add Bible Study files
2024-10-30 add hang in there cat
2024-10-30 Fixed width images
    Fixed width images
    refreshed all images with full resolution copies
2024-10-31 add the Internt
2024-10-31 Add Scratch and Sniff files
2024-10-31 change image width
2024-10-31 create checkpoint party files
2024-10-31 add i almost died badge
2024-10-31 Add I almost DIED badge files
2024-10-31 add pics and update height
2024-10-31 fix2
2024-11-01 add framework schematic
2024-11-01 Rename Expansion_Card_Template_X1.zip to Expansion_Card_Minibadge.zip
2024-11-07 Add 3x3 grid files
2024-11-09 r3 (on/off, graphics, laser cut files)
2024-11-09 Moved files to correct flder
2024-11-20 Add doug and Flipper Zero addon
2024-12-03 Create BEEP BEEP minibadge
2024-12-03 add buzzer minibadge files
2024-12-04 add ATTiny devobard files
2024-12-18 add morse code blink
2024-12-18 Rename folder
2024-12-18 Board revision R5
2024-12-24 R6
    Add diode for reverse polarity protection
2025-07-16 add crown burger minibadge
2025-07-16 Rename logo
2025-07-28 Add Minifridge
2025-07-28 Add Julia Reagan badge
2025-07-28 Remove Kicad Template
2025-07-28 Add Microbadge Minibadge
2025-07-28 Minifridge Minibadge
2025-08-14 Update Julia minibadge
2025-09-01 Add Camera Minibadge
2025-10-02 R2 Microbadge Minibadge
2025-10-02 update gitignore
2025-10-02 solder mask fixes
2025-10-02 julia renders
2025-10-05 Update graphics and add more finances
2025-10-15 donut display board
2025-10-15 connector board
2025-11-02 Add Bender
2025-11-11 Add XIAO ESP minibadge
2025-11-11 XIAO ESP32
2025-12-08 XIAO update
2025-12-25 it came to me in a dream
2026-01-01 update images
2026-01-01 add phone charger minibadge
2026-01-01 Finalize rev1
2026-01-02 Update silkscreen positions and text in PCB layout
    Adjusted the positions of silkscreen reference designators for several components (R4, R5, R6, C1, C5, U1) and updated the vector font renderings for their labels in the KiCad PCB file. These changes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
2026-01-02 Add initial KiCad files for Perfboard minibadge
    Added schematic (.kicad_sch), PCB layout (.kicad_pcb), and project (.kicad_pro) files for the Perfboard minibadge project. This includes the board outline, footprints, and net definitions for the ini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
2026-01-02 Add IPEX to SMA minibadge KiCad project files
    Initial commit of the IPEX to SMA minibadge project, including schematic (.kicad_sch), PCB layout (.kicad_pcb), and project file (.kicad_pro).
2026-01-02 Add IPEX to SMA adapter minibadge information
    Added IPEX to SMA adapter minibadge details including images and description.
2026-01-02 Add images to IPEX to SMA adapter Minibadge
    Added two new images to the IPEX to SMA adapter section.
